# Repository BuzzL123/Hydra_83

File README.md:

# Hydra 83

> _One board. Two protocols. More to come._

---

## What Is It?

The **Hydra 83** is a custom 83-key mechanical keyboard that can switch between **USB HID** and **PS/2** via a hardware toggle. The name comes from two things:

- **83** — the total key count
- **Hydra** — the multi-headed creature of myth, representing the board's ability to switch between protocols. In PS/2 mode it's a standard PS/2 keyboard; in USB mode it's a USB keyboard that also accepts a PS/2 mouse on the PS/2 connector

The Hydra is intended to be a series. Future versions may add an integrated USB hub, additional protocol modes, or other switching features.

---

## Features

- **Dual-protocol keyboard output** — USB HID or PS/2 Scan Code Set 2, selected with a hardware toggle
- **PS/2 mouse input in USB mode** — plug a PS/2 mouse into the PS/2 connector while in USB mode; QMK's built-in PS/2 mouse driver reads it and forwards it to the host over USB
- **Full PS/2 keyboard implementation** — make/break codes, typematic repeat, E0-prefixed extended keys, F13–F24, multimedia, browser, and power keys
- **On-board BSS138 level shifters** — two BSS138 MOSFETs handle bidirectional 3.3 V ↔ 5 V translation on the PS/2 clock and data lines; no external components needed
- **OLED display** — SSD1306 128×32 connected via I2C
- **Rotary encoder** — Alps EC11E with push-to-click
- **USB-C connector** — with SRV05-4 ESD protection
- **Hardware mode switch** — debounced in firmware (50 ms)
- **QMK-based firmware** — fully remappable, built on QMK best practices, using QMK built-ins wherever possible

---

## How the Modes Work

### PS/2 Mode

The board operates as a standard PS/2 keyboard. Connect it to any PS/2 port — Scan Code Set 2, typematic repeat, full extended key support, all modifiers. The PS/2 clock and data lines are driven by the RP2040 through the BSS138 level shifters.

### USB Mode

The board enumerates as a USB HID keyboard. The PS/2 connector switches role: it becomes a **PS/2 mouse host**. Plug a PS/2 mouse in and QMK reads it and forwards mouse movement, buttons, and scroll to the host over USB alongside keyboard input — one USB-C cable, both devices.

---

## Layout

The Hydra 83 has 83 keys with an integrated numpad cluster, F1–F12 doubling as F13–F24, and a rotary encoder in the top-right corner.

---

## Repository Layout

```
├── Firmware/
│   ├── config.h
│   ├── halconf.h
│   ├── kb.c
│   ├── kb.h
│   ├── keyboard.json
│   ├── keymaps/
│   │   └── default/
│   │       └── keymap.c
│   ├── Makefile
│   ├── mcuconf.h
│   ├── ps2_keyboard.c
│   ├── ps2_keyboard.h
│   ├── ps2_scancodes.h
│   ├── readme.md
│   └── rules.mk
└── PCB/
    ├── gerbers/
    │   ├── bom.csv
    │   ├── designators.csv
    │   ├── Hydra_83_1.0.zip
    │   ├── netlist.ipc
    │   └── positions.csv
    ├── Hydra83_Schamatics.pdf
    ├── Hydra83__Assembly.pdf
    ├── ibom.html
    ├── kicad/
    │   ├── fabrication-toolkit-options.json
    │   ├── fp-lib-table
    │   ├── Hydra83.kicad_pcb
    │   ├── Hydra83.kicad_prl
    │   ├── Hydra83.kicad_pro
    │   ├── Hydra83.kicad_sch
    │   ├── Hydra83.net
    │   ├── kbplacer.log
    │   └── sch_data.json
    └── layout.png
```

PS/2 mouse host support uses QMK's built-in `PS2_MOUSE` feature, enabled in `rules.mk`.

---

## Hardware

### Key Components

|Ref|Part|Description|
|---|---|---|
|U3|RP2040|Microcontroller|
|U4|W25Q128JVS|128 Mbit external flash|
|U1|XC6206PxxxMR|3.3 V LDO regulator|
|U2, U6|SRV05-4|USB ESD protection|
|Q1, Q2|BSS138|PS/2 bidirectional level shifters|
|J2|USB-C receptacle|USB 2.0, 16-pin|
|P1|Mini-DIN 6-pin|PS/2 connector|
|J3|SSD1306|0.91" 128×32 OLED (I2C)|
|Y1|12 MHz crystal|RP2040 clock source|
|SW1|Tactile switch|BOOTSEL|
|SW2|Tactile switch|RESET|
|SW3|Toggle / jumper|Mode select (USB / PS/2)|
|RE1|Alps EC11E|Rotary encoder with switch|

### GPIO Pin Map

All 30 RP2040 GPIOs are used:

|GPIO|Signal|Notes|
|---|---|---|
|GP0|Row_0|Key matrix|
|GP1|Row_1||
|GP2|Row_2||
|GP3|Row_3||
|GP4|Row_4||
|GP5|Column_0||
|GP6|Column_1||
|GP7|Column_2||
|GP8|Column_3||
|GP9|Column_4||
|GP10|Column_5||
|GP11|Column_6||
|GP12|Column_7||
|GP13|Column_8||
|GP14|Column_9||
|GP15|Column_10||
|GP16|Column_11||
|GP17|Column_12||
|GP18|Column_13||
|GP19|Column_14||
|GP20|Column_15||
|GP21|Column_16||
|GP22|Column_17||
|GP23|Mode_Switch|HIGH = USB, LOW = PS/2|
|GP24|PS/2_Data|Through BSS138 level shifter|
|GP25|PS/2_Clock|Through BSS138 level shifter|
|GP26|I2C1_SDA|OLED (SSD1306)|
|GP27|I2C1_SCL|OLED (SSD1306)|
|GP28|Encoder_Up|Rotary encoder A|
|GP29|Encoder_Down|Rotary encoder B|

### PS/2 Connector Pinout (Mini-DIN 6)

|PS/2 Pin|Signal|Notes|
|---|---|---|
|1|Data|Through BSS138 to GP24|
|3|GND||
|4|VCC|VBUS (5 V)|
|5|Clock|Through BSS138 to GP25|

---

## PCB

KiCad source files, schematic PDF, PCB plot PDF, interactive HTML BOM (`ibom.html`), and JLCPCB fabrication files are all in the `PCB/` directory. The design is still being refined.

To view the interactive BOM, open `ibom.html` in any browser — it shows component placement on the board alongside the BOM table, useful for hand assembly.

---

## Firmware

### Prerequisites

- [QMK Firmware](https://docs.qmk.fm/#/newbs_getting_started) set up locally
- QMK CLI configured
- ARM GCC toolchain (installed by `qmk setup`)

### Build & Flash

```bash
# Copy the Firmware folder into your QMK keyboards directory
cd ~/qmk_firmware/keyboards
mkdir -p hydra83
cp -r /path/to/Hydra_83/Firmware hydra83/hydra83

# Compile
qmk compile -kb hydra83/hydra83 -km default

# Flash — double-tap reset on RP2040 to enter bootloader, then:
qmk flash -kb hydra83/hydra83 -km default
```

Or copy the pre-compiled `.uf2` from the [Releases](https://github.com/BuzzL123/Hydra_83/releases) page onto the `RPI-RP2` drive.

### Keymap Customization

Edit `Firmware/keymaps/default/keymap.c`. Full PS/2 Scan Code Set 2 support is already in the firmware — just change the layout array.

---

## Debugging

```bash
qmk console
```

```
================================
Mode switch: PS/2
================================
[PS2] PS/2 driver activated
[PS2] Key pressed: keycode=0x0004, scancode=0x1C
[PS2] Typematic repeat: keycode=0x0004, scancode=0x1C
[PS2] Key released: keycode=0x0004, scancode=0x1C
================================
Mode switch: USB
================================
[USB] USB driver restored
```

---

## PS/2 Protocol Details

The keyboard side operates in PS/2 **device** mode — the RP2040 acts _as_ a keyboard. Each byte is 11 bits (start, 8 data bits LSB-first, odd parity, stop) at ~10 kHz. The firmware handles:

- Make codes (key down) and break codes (`0xF0` + scancode, key up)
- E0-prefixed extended codes for arrows, navigation, multimedia, browser, and power keys
- Multi-byte sequences for Print Screen and Pause/Break
- Typematic repeat — 500 ms initial delay, ~30 repeats/second

In USB mode the same PS/2 lines (GP24/GP25) switch to input, and QMK's `PS2_MOUSE` driver reads standard PS/2 mouse packets and forwards them over USB HID.

---

## Roadmap

- [ ] Finalize PCB layout
- [ ] Software mode toggle via keypress (in addition to hardware switch)

---

## Contributing

Pull requests are welcome. Open an issue first for significant changes.

---

## License

GPL-2.0 — see LICENSE. Matches the QMK Firmware license for full compatibility.

---

## Author

**Betzalel J. Lewis** — [GitHub](https://github.com/BuzzL123)

_PS/2 device mode proof-of-concept: [QMK PS/2 USB Dual-Mode Keyboard](https://github.com/BuzzL123/QMK-PS2-USB-Dual-Mode-Keyboard)_

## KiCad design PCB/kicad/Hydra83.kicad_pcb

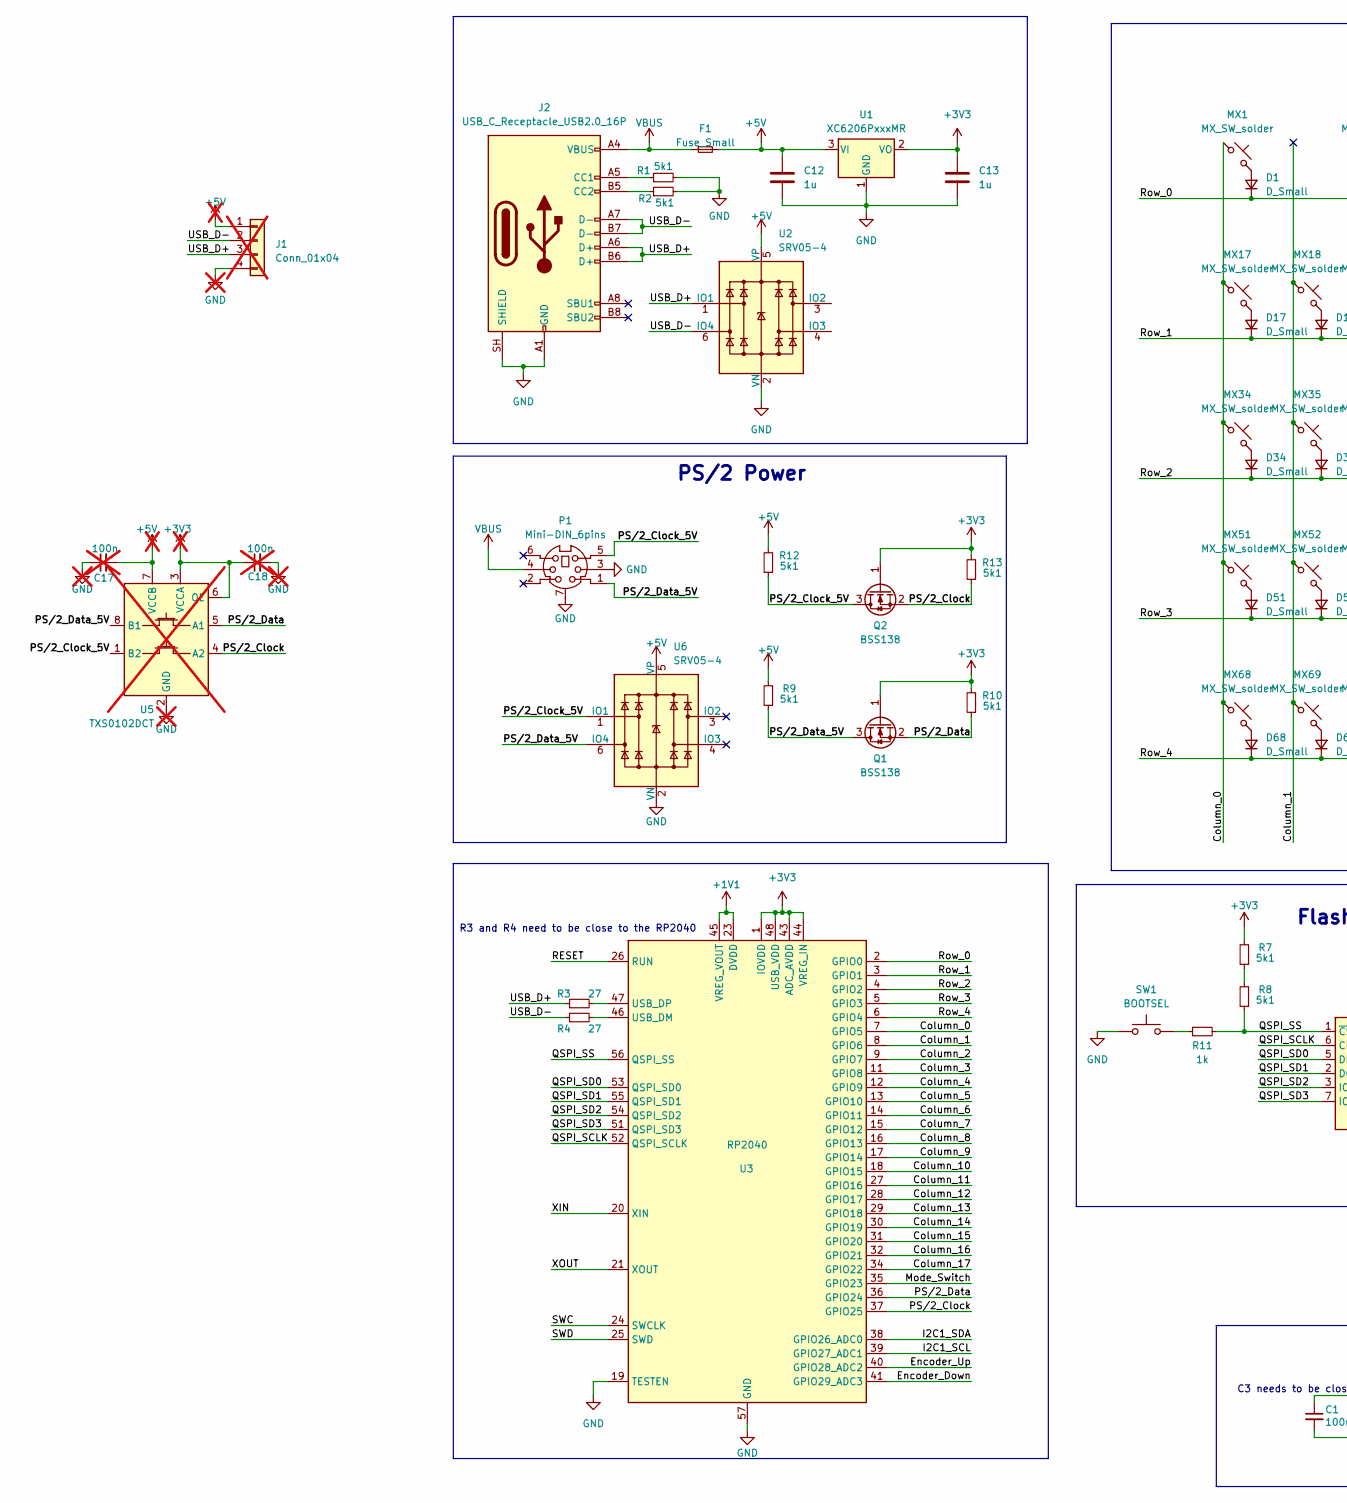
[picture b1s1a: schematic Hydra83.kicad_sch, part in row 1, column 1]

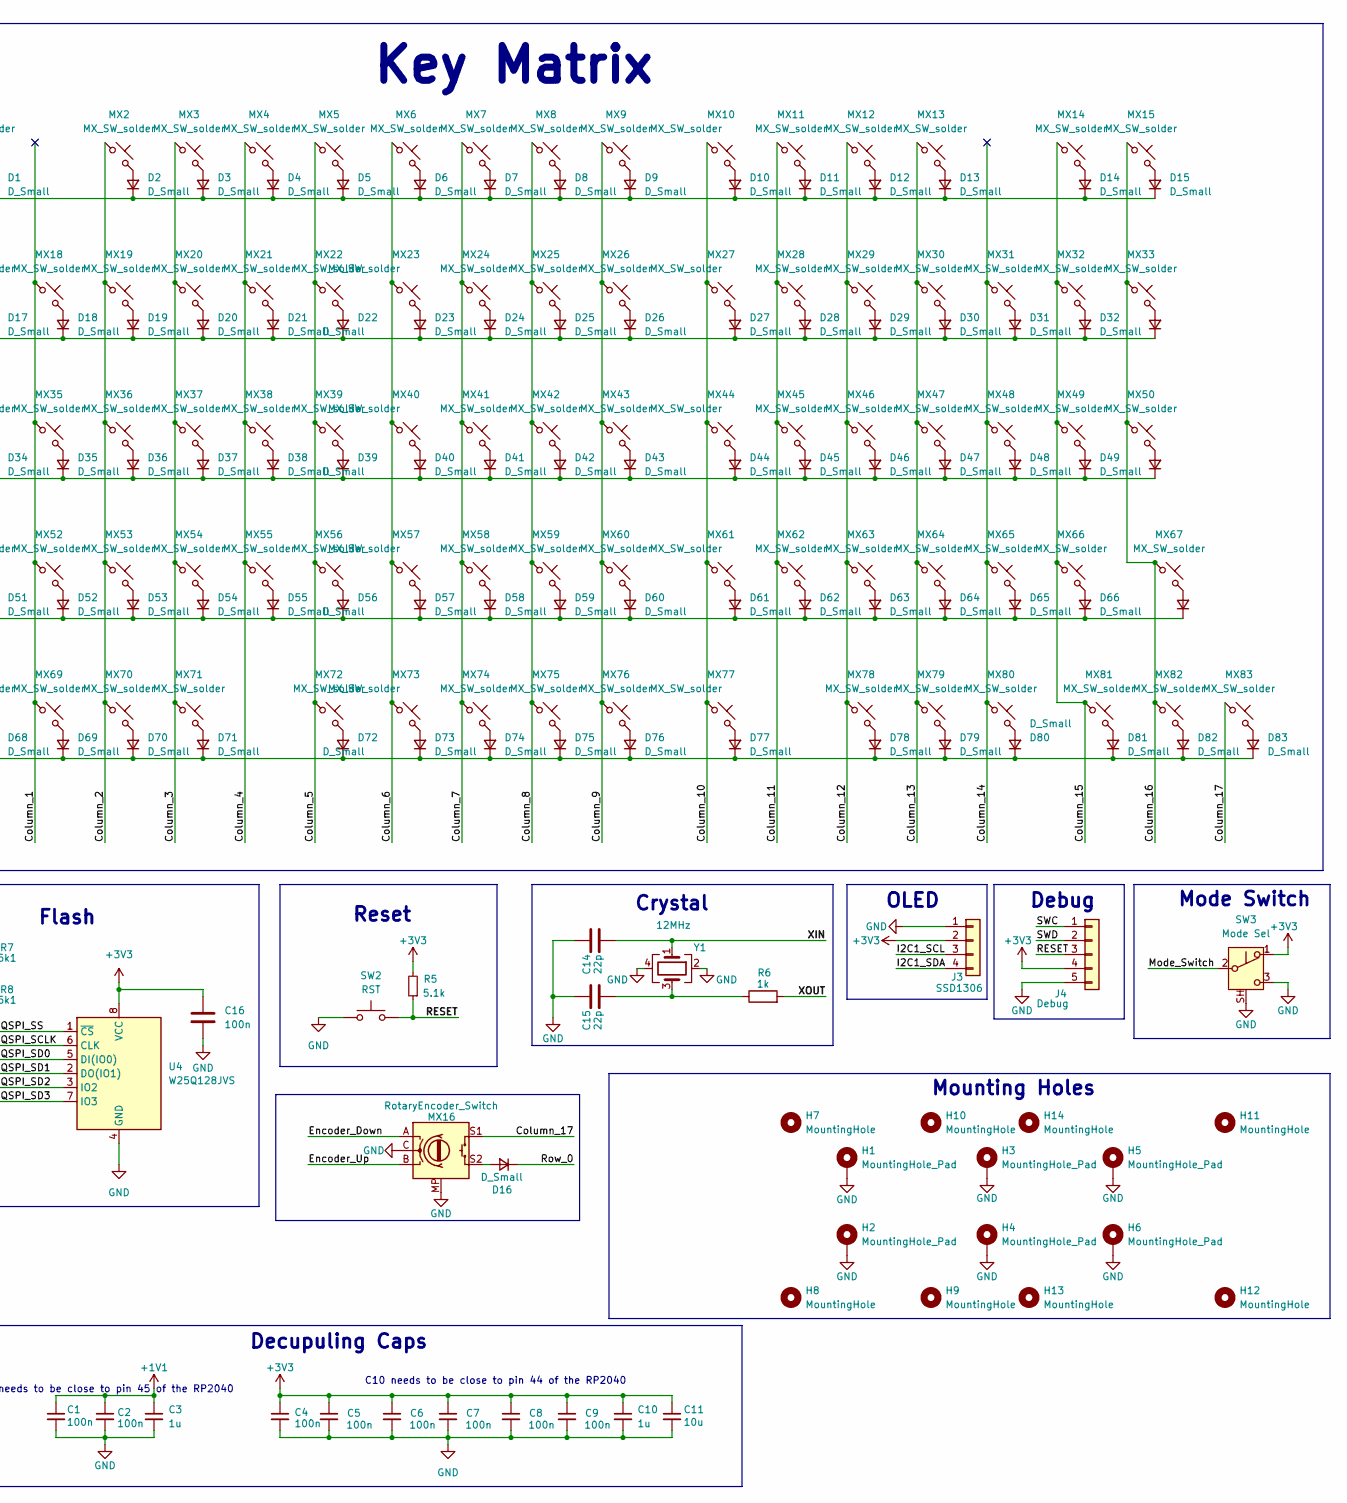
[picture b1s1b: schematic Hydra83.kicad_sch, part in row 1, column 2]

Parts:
C1, C2, C4, C5, C6, C7, C8, C9, C16: 100n; C_0402_1005Metric
C3, C10, C12, C13: 1u; C_0402_1005Metric
C11: 10u; C_0603_1608Metric
C14, C15: 22p; C_0402_1005Metric
C17, C18: 100n; C_0402_1005Metric; not fitted
D1, D2, D3, D4, D5, D6, D7, D8, D9, D10, D11, D12, D13, D14, D15, D16, D17, D18, D19, D20, D21, D22, D23, D24, D25, D26, D27, D28, D29, D30, D31, D32, D33, D34, D35, D36, D37, D38, D39, D40, D41, D42, D43, D44, D45, D46, D47, D48, D49, D50, D51, D52, D53, D54, D55, D56, D57, D58, D59, D60, D61, D62, D63, D64, D65, D66, D67, D68, D69, D70, D71, D72, D73, D74, D75, D76, D77, D78, D79, D80, D81, D82, D83: D_Small; D_SOD-123
F1: Fuse_Small; Fuse_1206_3216Metric
H1, H2, H3, H4, H5, H6: MountingHole_Pad; MountingHole_3.2mm_M3_Pad
H7, H8, H9, H10, H11, H12, H13, H14: MountingHole; MountingHole_3.2mm_M3
J1: Conn_01x04; JST_SH_SM04B-SRSS-TB_1x04-1MP_P1.00mm_Horizontal; not fitted
J2: USB_C_Receptacle_USB2.0_16P; USB_C_Receptacle_HRO_TYPE-C-31-M-12
J3: SSD1306; SSD1306-0.91-OLED-4pin-128x32
J4: Debug; PinHeader_1x05_P2.54mm_Vertical
MX1, MX2, MX3, MX4, MX5, MX6, MX7, MX8, MX9, MX10, MX11, MX12, MX13, MX14, MX15, MX17, MX18, MX19, MX20, MX21, MX22, MX23, MX24, MX25, MX26, MX27, MX28, MX29, MX30, MX31, MX32, MX33, MX34, MX35, MX36, MX37, MX38, MX39, MX40, MX41, MX42, MX43, MX44, MX45, MX46, MX47, MX48, MX49, MX50, MX51, MX52, MX53, MX54, MX55, MX56, MX57, MX58, MX59, MX60, MX61, MX62, MX63, MX64, MX65, MX66, MX67, MX68, MX69, MX70, MX71, MX73, MX74, MX75, MX76, MX78, MX79, MX80, MX81, MX82, MX83: MX_SW_solder; SW_MX_1u
MX16: RotaryEncoder_Switch; RotaryEncoder_Alps_EC11E-Switch_Vertical_H20mm
MX72, MX77: MX_SW_solder; SW_MX_1.75u
P1: Mini-DIN_6pins; Connector_Mini-DIN_Female_6Pin_2rows
Q1, Q2: BSS138; SOT-23
R1, R2, R7, R8, R9, R10, R12, R13: 5k1; R_0402_1005Metric
R3, R4: 27; R_0402_1005Metric
R5: 5.1k; R_0402_1005Metric
R6, R11: 1k; R_0402_1005Metric
SW1: BOOTSEL; SW_SPST_TL3342
SW2: RST; SW_SPST_TL3342
SW3: Mode Sel; SW_Slide_SPDT_Angled_CK_OS102011MA1Q
U1: XC6206PxxxMR; SOT-23-3
U2, U6: SRV05-4; SOT-23-6-routable
U3: RP2040; QFN-56-1EP_7x7mm_P0.4mm_EP3.2x3.2mm_ThermalVias
U4: W25Q128JVS; SOIC-8_5.3x5.3mm_P1.27mm
U5: TXS0102DCT; SSOP-8_2.95x2.8mm_P0.65mm; not fitted
Y1: 12MHz; Crystal_SMD_3225-4Pin_3.2x2.5mm

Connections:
+1V1: C1.1, C2.1, C3.1, U3.23 (DVDD), U3.45 (VREG_VOUT), U3.50 (DVDD)
+3V3: C4.1, C5.1, C6.1, C7.1, C8.1, C9.1, C10.1, C11.1, C13.1, C16.1, C18.1, J3.2, J4.4, Q1.1 (G), Q2.1 (G), R5.2, R7.2, R10.2, R13.2, SW3.1 (A), U1.2 (VO), U3.1 (IOVDD), U3.10 (IOVDD), U3.22 (IOVDD), U3.33 (IOVDD), U3.42 (IOVDD), U3.43 (ADC_AVDD), U3.44 (VREG_IN), U3.48 (USB_VDD), U3.49 (IOVDD), U4.8 (VCC), U5.3 (VCCA), U5.6 (OE)
+5V: C12.1, C17.2, F1.2, J1.1, R9.2, R12.2, U1.3 (VI), U2.5 (VP), U5.7 (VCCB), U6.5 (VP)
/Column_0: MX1.1, MX17.1, MX34.1, MX51.1, MX68.1, U3.7 (GPIO5)
/Column_1: MX18.1, MX35.1, MX52.1, MX69.1, U3.8 (GPIO6)
/Column_2: MX2.1, MX19.1, MX36.1, MX53.1, MX70.1, U3.9 (GPIO7)
/Column_3: MX3.1, MX20.1, MX37.1, MX54.1, MX71.1, U3.11 (GPIO8)
/Column_4: MX4.1, MX21.1, MX38.1, MX55.1, U3.12 (GPIO9)
/Column_5: MX5.1, MX22.1, MX39.1, MX56.1, MX72.1, U3.13 (GPIO10)
/Column_6: MX6.1, MX23.1, MX40.1, MX57.1, MX73.1, U3.14 (GPIO11)
/Column_7: MX7.1, MX24.1, MX41.1, MX58.1, MX74.1, U3.15 (GPIO12)
/Column_8: MX8.1, MX25.1, MX42.1, MX59.1, MX75.1, U3.16 (GPIO13)
/Column_9: MX9.1, MX26.1, MX43.1, MX60.1, MX76.1, U3.17 (GPIO14)
/Column_10: MX10.1, MX27.1, MX44.1, MX61.1, MX77.1, U3.18 (GPIO15)
/Column_11: MX11.1, MX28.1, MX45.1, MX62.1, U3.27 (GPIO16)
/Column_12: MX12.1, MX29.1, MX46.1, MX63.1, MX78.1, U3.28 (GPIO17)
/Column_13: MX13.1, MX30.1, MX47.1, MX64.1, MX79.1, U3.29 (GPIO18)
/Column_14: MX31.1, MX48.1, MX65.1, MX80.1, U3.30 (GPIO19)
/Column_15: MX14.1, MX32.1, MX49.1, MX66.1, MX81.1, U3.31 (GPIO20)
/Column_16: MX15.1, MX33.1, MX50.1, MX67.1, MX82.1, U3.32 (GPIO21)
/Column_17: MX16.S1, MX83.1, U3.34 (GPIO22)
/Encoder_Down: MX16.A, U3.41 (GPIO29_ADC3)
/Encoder_Up: MX16.B, U3.40 (GPIO28_ADC2)
/I2C1_SCL: J3.3, U3.39 (GPIO27_ADC1)
/I2C1_SDA: J3.4, U3.38 (GPIO26_ADC0)
/Mode_Switch: SW3.2 (B), U3.35 (GPIO23)
/PS/2_Clock: Q2.2 (S), R13.1, U3.37 (GPIO25), U5.4 (A2)
/PS/2_Clock_5V: P1.5, Q2.3 (D), R12.1, U5.1 (B2), U6.1 (IO1)
/PS/2_Data: Q1.2 (S), R10.1, U3.36 (GPIO24), U5.5 (A1)
/PS/2_Data_5V: P1.1, Q1.3 (D), R9.1, U5.8 (B1), U6.6 (IO4)
/QSPI_SCLK: U3.52 (QSPI_SCLK), U4.6 (CLK)
/QSPI_SD0: U3.53 (QSPI_SD0), U4.5 (DI(IO0))
/QSPI_SD1: U3.55 (QSPI_SD1), U4.2 (DO(IO1))
/QSPI_SD2: U3.54 (QSPI_SD2), U4.3 (IO2)
/QSPI_SD3: U3.51 (QSPI_SD3), U4.7 (IO3)
/QSPI_SS: R8.1, R11.2, U3.56 (QSPI_SS), U4.1 (~CS)
/RESET: J4.3, R5.1, SW2.2, U3.26 (RUN)
/Row_0: D1.1 (K), D2.1 (K), D3.1 (K), D4.1 (K), D5.1 (K), D6.1 (K), D7.1 (K), D8.1 (K), D9.1 (K), D10.1 (K), D11.1 (K), D12.1 (K), D13.1 (K), D14.1 (K), D15.1 (K), D16.1 (K), U3.2 (GPIO0)
/Row_1: D17.1 (K), D18.1 (K), D19.1 (K), D20.1 (K), D21.1 (K), D22.1 (K), D23.1 (K), D24.1 (K), D25.1 (K), D26.1 (K), D27.1 (K), D28.1 (K), D29.1 (K), D30.1 (K), D31.1 (K), D32.1 (K), D33.1 (K), U3.3 (GPIO1)
/Row_2: D34.1 (K), D35.1 (K), D36.1 (K), D37.1 (K), D38.1 (K), D39.1 (K), D40.1 (K), D41.1 (K), D42.1 (K), D43.1 (K), D44.1 (K), D45.1 (K), D46.1 (K), D47.1 (K), D48.1 (K), D49.1 (K), D50.1 (K), U3.4 (GPIO2)
/Row_3: D51.1 (K), D52.1 (K), D53.1 (K), D54.1 (K), D55.1 (K), D56.1 (K), D57.1 (K), D58.1 (K), D59.1 (K), D60.1 (K), D61.1 (K), D62.1 (K), D63.1 (K), D64.1 (K), D65.1 (K), D66.1 (K), D67.1 (K), U3.5 (GPIO3)
/Row_4: D68.1 (K), D69.1 (K), D70.1 (K), D71.1 (K), D72.1 (K), D73.1 (K), D74.1 (K), D75.1 (K), D76.1 (K), D77.1 (K), D78.1 (K), D79.1 (K), D80.1 (K), D81.1 (K), D82.1 (K), D83.1 (K), U3.6 (GPIO4)
/SWC: J4.1, U3.24 (SWCLK)
/SWD: J4.2, U3.25 (SWD)
/USB_D+: J1.3, J2.A6 (D+), J2.B6 (D+), R3.1, U2.1 (IO1)
/USB_D-: J1.2, J2.A7 (D-), J2.B7 (D-), R4.1, U2.6 (IO4)
/XIN: C14.2, U3.20 (XIN), Y1.1
/XOUT: R6.2, U3.21 (XOUT)
GND: C1.2, C2.2, C3.2, C4.2, C5.2, C6.2, C7.2, C8.2, C9.2, C10.2, C11.2, C12.2, C13.2, C14.1, C15.1, C16.2, C17.1, C18.2, H1.1 (1_1), H2.1 (1_1), H3.1 (1_1), H4.1 (1_1), H5.1 (1_1), H6.1 (1_1), J1.4, J2.A1 (GND), J2.A12 (GND), J2.B1 (GND), J2.B12 (GND), J2.SH (SHIELD), J3.1, J4.5, MX16.C, MX16.MP, P1.3, P1.7 (Shell), R1.2, R2.2, SW1.1, SW2.1, SW3.3 (C), SW3.SH, U1.1 (GND), U2.2 (VN), U3.19 (TESTEN), U3.57 (GND), U4.4 (GND), U5.2 (GND), U6.2 (VN), Y1.2, Y1.4
unnamed: C15.2, R6.1, Y1.3
unnamed: D1.2 (A), MX1.2
unnamed: D2.2 (A), MX2.2
unnamed: D3.2 (A), MX3.2
unnamed: D4.2 (A), MX4.2
unnamed: D5.2 (A), MX5.2
unnamed: D6.2 (A), MX6.2
unnamed: D7.2 (A), MX7.2
unnamed: D8.2 (A), MX8.2
unnamed: D9.2 (A), MX9.2
unnamed: D10.2 (A), MX10.2
unnamed: D11.2 (A), MX11.2
unnamed: D12.2 (A), MX12.2
unnamed: D13.2 (A), MX13.2
unnamed: D14.2 (A), MX14.2
unnamed: D15.2 (A), MX15.2
unnamed: D16.2 (A), MX16.S2
unnamed: D17.2 (A), MX17.2
unnamed: D18.2 (A), MX18.2
unnamed: D19.2 (A), MX19.2
unnamed: D20.2 (A), MX20.2
unnamed: D21.2 (A), MX21.2
unnamed: D22.2 (A), MX22.2
unnamed: D23.2 (A), MX23.2
unnamed: D24.2 (A), MX24.2
unnamed: D25.2 (A), MX25.2
unnamed: D26.2 (A), MX26.2
unnamed: D27.2 (A), MX27.2
unnamed: D28.2 (A), MX28.2
unnamed: D29.2 (A), MX29.2
unnamed: D30.2 (A), MX30.2
unnamed: D31.2 (A), MX31.2
unnamed: D32.2 (A), MX32.2
unnamed: D33.2 (A), MX33.2
unnamed: D34.2 (A), MX34.2
unnamed: D35.2 (A), MX35.2
unnamed: D36.2 (A), MX36.2
unnamed: D37.2 (A), MX37.2
unnamed: D38.2 (A), MX38.2
unnamed: D39.2 (A), MX39.2
unnamed: D40.2 (A), MX40.2
unnamed: D41.2 (A), MX41.2
unnamed: D42.2 (A), MX42.2
unnamed: D43.2 (A), MX43.2
unnamed: D44.2 (A), MX44.2
unnamed: D45.2 (A), MX45.2
unnamed: D46.2 (A), MX46.2
unnamed: D47.2 (A), MX47.2
unnamed: D48.2 (A), MX48.2
unnamed: D49.2 (A), MX49.2
unnamed: D50.2 (A), MX50.2
unnamed: D51.2 (A), MX51.2
unnamed: D52.2 (A), MX52.2
unnamed: D53.2 (A), MX53.2
unnamed: D54.2 (A), MX54.2
unnamed: D55.2 (A), MX55.2
unnamed: D56.2 (A), MX56.2
unnamed: D57.2 (A), MX57.2
unnamed: D58.2 (A), MX58.2
unnamed: D59.2 (A), MX59.2
unnamed: D60.2 (A), MX60.2
unnamed: D61.2 (A), MX61.2
unnamed: D62.2 (A), MX62.2
unnamed: D63.2 (A), MX63.2
unnamed: D64.2 (A), MX64.2
unnamed: D65.2 (A), MX65.2
unnamed: D66.2 (A), MX66.2
unnamed: D67.2 (A), MX67.2
unnamed: D68.2 (A), MX68.2
unnamed: D69.2 (A), MX69.2
unnamed: D70.2 (A), MX70.2
unnamed: D71.2 (A), MX71.2
unnamed: D72.2 (A), MX72.2
unnamed: D73.2 (A), MX73.2
unnamed: D74.2 (A), MX74.2
unnamed: D75.2 (A), MX75.2
unnamed: D76.2 (A), MX76.2
unnamed: D77.2 (A), MX77.2
unnamed: D78.2 (A), MX78.2
unnamed: D79.2 (A), MX79.2
unnamed: D80.2 (A), MX80.2
unnamed: D81.2 (A), MX81.2
unnamed: D82.2 (A), MX82.2
unnamed: D83.2 (A), MX83.2
unnamed: J2.A5 (CC1), R1.1
unnamed: J2.B5 (CC2), R2.1
unnamed: R7.1, R8.2
unnamed: R11.1, SW1.2
unnamed: R4.2, U3.46 (USB_DM)
unnamed: R3.2, U3.47 (USB_DP)
VBUS: F1.1, J2.A4 (VBUS), J2.A9 (VBUS), J2.B4 (VBUS), J2.B9 (VBUS), P1.4

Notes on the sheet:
Debug
OLED
Decupuling Caps
Crystal
R3 and R4 need to be close to the RP2040
Mode Switch
C3 needs to be close to pin 45 of the RP2040
Flash
Reset
PS/2 Power
C10 needs to be close to pin 44 of the RP2040
Mounting Holes
Key Matrix

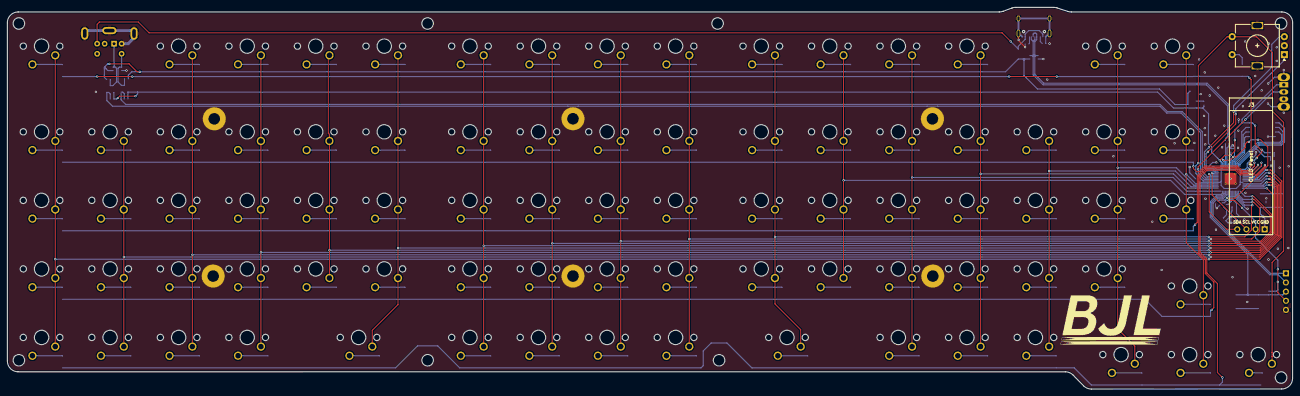
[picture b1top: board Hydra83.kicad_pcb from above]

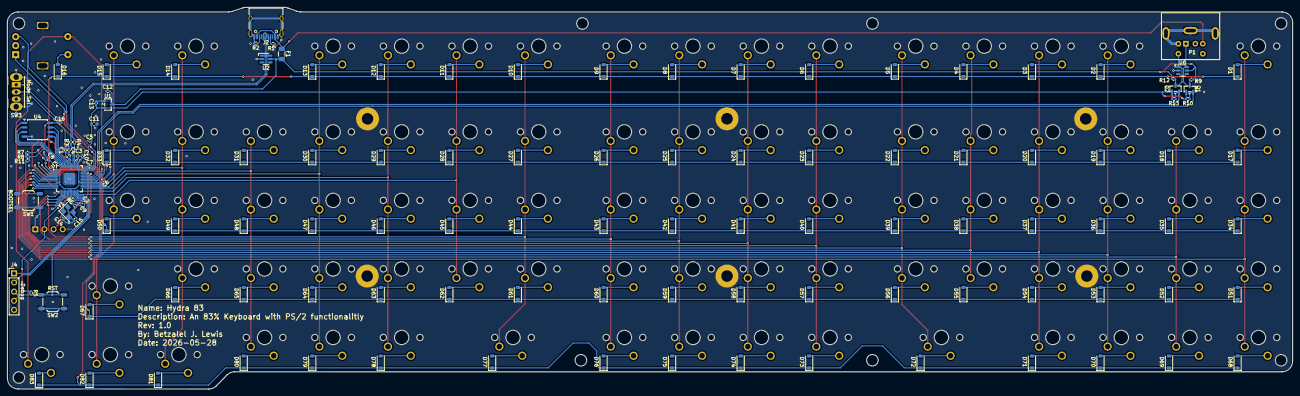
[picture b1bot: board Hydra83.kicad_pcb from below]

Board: 2 copper layers, 357.2 x 106.1 mm, 225 parts (127 on the bottom side), 140 nets.

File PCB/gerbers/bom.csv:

Designator,Footprint,Quantity,Value,LCSC Part #
"C1, C16, C2, C4, C5, C6, C7, C8, C9",402,9,100n,C60474
"C10, C12, C13, C3",402,4,1u,C14445
C11,603,1,10u,C19702
"C14, C15",402,2,22p,C106203
"D1, D10, D11, D12, D13, D14, D15, D16, D17, D18, D19, D2, D20, D21, D22, D23, D24, D25, D26, D27, D28, D29, D3, D30, D31, D32, D33, D34, D35, D36, D37, D38, D39, D4, D40, D41, D42, D43, D44, D45, D46, D47, D48, D49, D5, D50, D51, D52, D53, D54, D55, D56, D57, D58, D59, D6, D60, D61, D62, D63, D64, D65, D66, D67, D68, D69, D7, D70, D71, D72, D73, D74, D75, D76, D77, D78, D79, D8, D80, D81, D82, D83, D9",D_SOD-123,83,D_Small,C83528
F1,1206,1,Fuse_Small,C83798
J2,USB_C_Receptacle_HRO_TYPE-C-31-M-12,1,USB_C_Receptacle_USB2.0_16P,C2765186
J3,SSD1306-0.91-OLED-4pin-128x32,1,SSD1306,
J4,PinHeader_1x05_P2.54mm_Vertical,1,Debug,
"MX1, MX10, MX11, MX12, MX13, MX14, MX15, MX17, MX18, MX19, MX2, MX20, MX21, MX22, MX23, MX24, MX25, MX26, MX27, MX28, MX29, MX3, MX30, MX31, MX32, MX33, MX34, MX35, MX36, MX37, MX38, MX39, MX4, MX40, MX41, MX42, MX43, MX44, MX45, MX46, MX47, MX48, MX49, MX5, MX50, MX51, MX52, MX53, MX54, MX55, MX56, MX57, MX58, MX59, MX6, MX60, MX61, MX62, MX63, MX64, MX65, MX66, MX67, MX68, MX69, MX7, MX70, MX71, MX73, MX74, MX75, MX76, MX78, MX79, MX8, MX80, MX81, MX82, MX83, MX9",SW_MX_1u,80,MX_SW_solder,
MX16,RotaryEncoder_Alps_EC11E-Switch_Vertical_H20mm,1,RotaryEncoder_Switch,
"MX72, MX77",SW_MX_1.75u,2,MX_SW_solder,
P1,Connector_Mini-DIN_Female_6Pin_2rows,1,Mini-DIN_6pins,C7428703
"Q1, Q2",SOT-23,2,BSS138,C52895
"R1, R10, R12, R13, R2, R7, R8, R9",402,8,5k1,C105872
"R11, R6",402,2,1k,C106235
"R3, R4",402,2,27,C138021
R5,402,1,5.1k,C105872
SW1,SW_SPST_TL3342,1,BOOTSEL,C318884
SW2,SW_SPST_TL3342,1,RST,C318884
SW3,SW_Slide_SPDT_Angled_CK_OS102011MA1Q,1,Mode Sel,C221530
U1,SOT-23-3,1,XC6206PxxxMR,C5446
"U2, U6",SOT-23-6-routable,2,SRV05-4,C151305
U3,QFN-56-1EP_7x7mm_P0.4mm_EP3.2x3.2mm_ThermalVias,1,RP2040,C2040
U4,SOIC-8_5.3x5.3mm_P1.27mm,1,W25Q128JVS,C97521
Y1,Crystal_SMD_3225-4Pin_3.2x2.5mm,1,12MHz,C9002

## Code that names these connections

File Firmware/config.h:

#pragma once

#define RP2040_BOOTLOADER_DOUBLE_TAP_RESET
#define RP2040_BOOTLOADER_DOUBLE_TAP_RESET_TIMEOUT 200U
#define RP2040_BOOTLOADER_DOUBLE_TAP_RESET_LED GP25

#define NO_USB_STARTUP_CHECK true

/* Shared PS/2 Port Pins */
#define PS2_CLOCK_PIN   GP25
#define PS2_DATA_PIN    GP24
#define MODE_SWITCH_PIN GP23

/* OLED */
#ifdef OLED_ENABLE
#define I2C1_SDA_PIN        GP26
#define I2C1_SCL_PIN        GP27
#define I2C_DRIVER          I2CD1
#define OLED_DISPLAY_128X32
#define OLED_BRIGHTNESS     128
#endif

/* GPIO Compatibility Shims for Modern QMK API */
#define setPinInput(pin)         gpio_set_pin_input(pin)
#define setPinInputHigh(pin)     gpio_set_pin_input_high(pin)
#define setPinInputLow(pin)      gpio_set_pin_input_low(pin)
#define setPinOutput(pin)        gpio_set_pin_output(pin)
#define writePinHigh(pin)        gpio_write_pin_high(pin)
#define writePinLow(pin)         gpio_write_pin_low(pin)
#define readPin(pin)             gpio_read_pin(pin)
#define togglePin(pin)           gpio_toggle_pin(pin)

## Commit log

2026-06-07 Enhance README with detailed Hydra 83 specifications
    Expanded the README to provide detailed information about the Hydra 83 keyboard, including its features, modes of operation, hardware components, and firmware setup instructions.
